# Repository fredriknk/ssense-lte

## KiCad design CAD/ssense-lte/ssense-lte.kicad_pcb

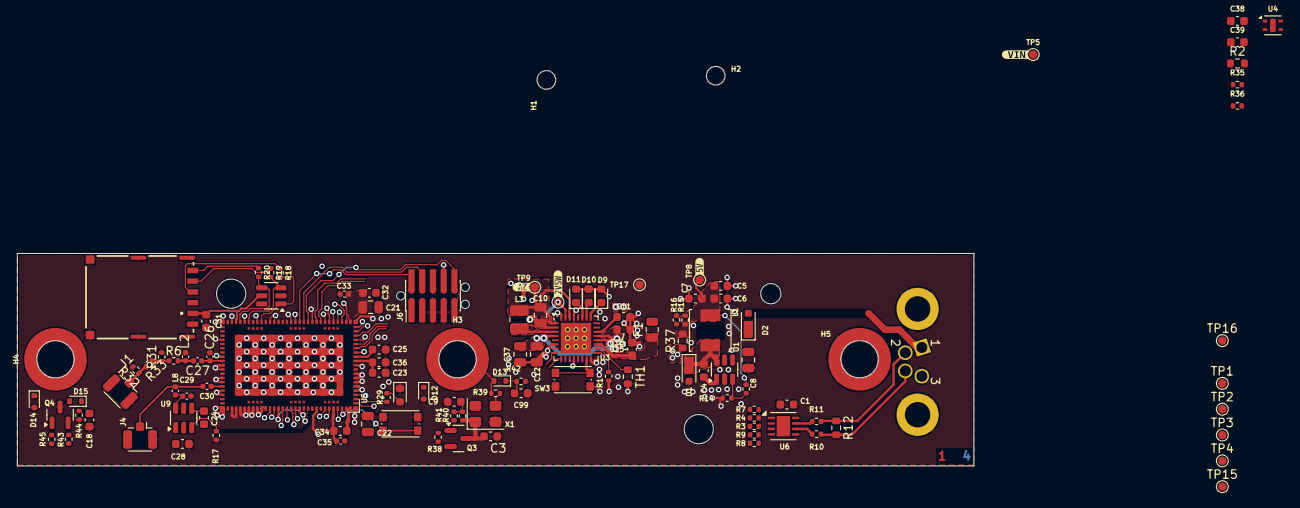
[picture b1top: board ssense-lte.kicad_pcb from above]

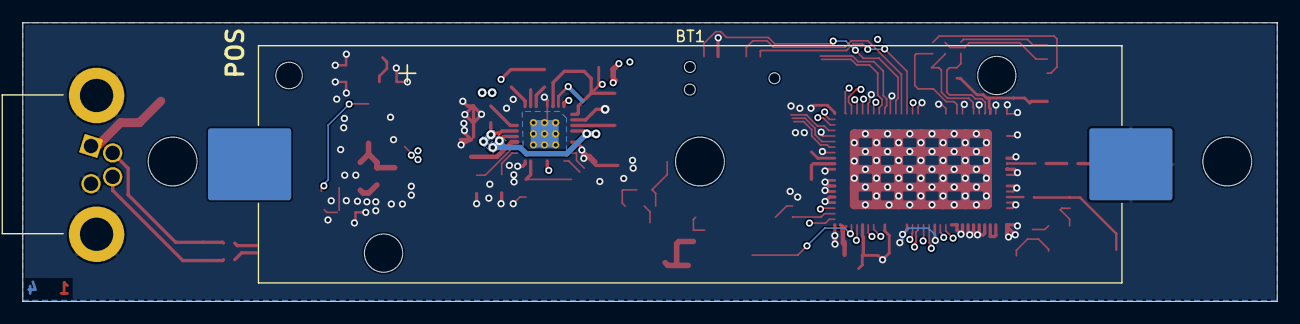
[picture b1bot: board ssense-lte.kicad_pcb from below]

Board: 4 copper layers, 113.0 x 25.1 mm, 123 parts (3 on the bottom side), 68 nets.

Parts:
BT1: Keystone 1042; BatteryHolder_Keystone_1042_1x18650
C1, C4, C32, C34, C36, C38: 0.1uF; C_0603_1608Metric
C3: 100nF; C_0603_1608Metric
C5, C6, C7, C15, C23, C25: 4.7uF; C_0603_1608Metric
C8: 2.2uF; C_0805_2012Metric
C9, C18, C24, C99: 1nF; C_0603_1608Metric
C10, C12, C37: 10uF; C_0805_2012Metric
C11, C16, C28, C31, C39: 1uF; C_0603_1608Metric
C21, C22: 47uF; C_0805_2012Metric
C26, C27, C33, C35: 15pF; C_0402_1005Metric_Sqr
C29, C30: 56pF; C_0402_1005Metric_Sqr
D1, D2: MSS1P3L-M3/89A; D_MicroSMP_AK
D7: LG L29K-G2J1-24-Z; LED_0603_1608Metric
D9, D10, D11: LED; LED_0603_1608Metric
D12, D14: Zener Prot 5V; D_SOD-523
D13, D15: CDSU101A; D_SOD-523
F1: 0805L110WR; Fuse_0805_2012Metric
H1, H2: MountingHole; MountingHole_2.2mm_M2
H3, H4, H5: 9774025360R; Mounting_Wuerth_WA-SMSI-M3_H2.5mm_9774025360
J1, J4: HIROSE ELECTRIC U.FL-R-SMT-1; U.FL_Hirose_U.FL-R-SMT-1_Vertical
J2: IEC61076-2_M8_A-coding_01x04_Receptacle_Shielded; STEWART_SS-12800-004_M8_04_Socket_Right_Angle
J3: 693043020611
J6: JLINK; SEXY_pinpogo
L1: 22uH; L_Abracon_AMDLA4020S
L2: 39NH; C_0402_1005Metric_Sqr
L3: 2.2uH; L_1008_2520Metric
L8: 68 nH; C_0402_1005Metric_Sqr
Q3: IRLML6401; SOT-23
Q4: MMBT3906; SOT-23
R1: 68k; R_0402_1005Metric
R2: 470R; R_0603_1608Metric
R3, R4, R14, R16, R35, R36, R38, R39, R40, R41, R43, R45: 10k; R_0402_1005Metric
R6, R7, R8, R9, R10, R11, R31, R32, R33: 0R; R_0402_1005Metric
R12: 120R; R_0603_1608Metric
R13: 56k; R_0402_1005Metric
R15: 15k; R_0402_1005Metric
R17, R42, R44: 1M; R_0402_1005Metric
R18, R19, R20: 100R; R_0402_1005Metric
R29: 150R; R_0402_1005Metric
R37: 0R; R_0603_1608Metric
SW1, SW3: KMR223NGLFG; SW_Push_1P1T_NO_CK_KMR2
TH1: 10k NTC; R_0603_1608Metric
TP1: SWDIO; TestPoint_Pad_D1.0mm
TP2: SWDCLK; TestPoint_Pad_D1.0mm
TP3: SWO; TestPoint_Pad_D1.0mm
TP4: RST; TestPoint_Pad_D1.0mm
TP5: VIN; TestPoint_Pad_D1.0mm
TP8: 5V; TestPoint_Pad_D1.0mm
TP9: 2V; TestPoint_Pad_D1.0mm
TP10: I1; TestPoint_Pad_D1.0mm
TP15, TP16, TP17: GND; TestPoint_Pad_D1.0mm
U1: LV2862XDDC; SOT-23-6
U3: nPM1300-QEXX; QFN-32-1EP_5x5mm_P0.5mm_EP3.6x3.6mm_ThermalVias
U4: SHTC3; Sensirion_DFN-4-1EP_2x2mm_P1mm_EP0.7x1.6mm
U5: nRF9160-SICA; LGA_9160_16.0x10.5mm
U6: THVD1450DR; VSON-8-1EP_3x3mm_P0.65mm_EP1.6x2.4mm
U8: USBLC6-4SC6; SOT-23-6
U9: TPS22917DBV; SOT-23-6
X1: KC3225K75.0000C1GE00; Oscillator_SMD_SeikoEpson_SG8002CE-4Pin_3.2x2.5mm
kibuzzard-680B6FC7: G***; kibuzzard-680B6FC7
kibuzzard-680B701D: G***; kibuzzard-680B701D
kibuzzard-680B714A: G***; kibuzzard-680B714A
kibuzzard-680B715D: G***; kibuzzard-680B715D
kibuzzard-689F1011: G***; kibuzzard-689F1011

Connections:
+1V8SIM: C31.1, J3.C1 (VCC), U5.49 (SIM_1V8), U8.5 (VBUS)
+3V3: C10.1, C23.1, C36.1, C38.1, C39.1, J6.1, L3.1, R35.2, R36.1, TP9.1, U3.1 (VOUT1), U3.12 (VDDIO), U3.30 (LSIN2/VINLDO2), U4.1 (VDD), U5.12 (VDD_GPIO)
+3V3SW: C1.1, TP10.1, U3.31 (LSOUT2/VOUTLDO2), U6.8 (VCC)
+3V6: Q3.2 (S), R38.1
+5V: C11.1, U3.22 (VBUSOUT)
+5VL: C16.1, R37.1, U3.21 (VBUS)
+12V: C8.1, D2.1 (K), U1.5 (VIN)
+BATT: C15.1, F1.1, U3.19 (VBAT)
/POWER/A': R10.1, U6.6 (A)
/POWER/A_P: J2.2, R11.2, R12.1
/POWER/B': R11.1, U6.7 (B)
/POWER/B_N: J2.4, R10.2, R12.2
/POWER/FB: R13.2, R14.1, U1.3 (FB)
/POWER/RE/DE': R3.2, R9.2, U6.2 (~RE), U6.3 (DE)
/POWER/RXD': R7.2, U6.1 (RO)
/POWER/SW: C4.2, D1.1 (K), L1.1, U1.6 (SW)
/POWER/SW1: L3.2, U3.3 (SW1)
/POWER/SW5V: C5.1, C6.1, C7.1, L1.2, R13.1, R15.1, R37.2, TP8.1
/POWER/TXD': R4.1, R8.2, U6.4 (DI)
/POWER/VIN: D2.2 (A), J2.1, TP5.1
/nrf9160/ANT: C26.1, C27.1, U5.61 (ANT)
/nrf9160/GPS_: C30.2, J4.1 (In), L8.1
COEX0: R17.2, U5.93 (COEX0), U9.3 (ON)
GND: BT1.2 (-), C1.2, C3.2, C5.2, C6.2, C7.2, C8.2, C9.2, C10.2, C11.2, C12.2, C15.2, C16.2, C18.2, C21.2, C22.2, C23.2, C25.2, C26.2, C28.2, C29.2, C31.2, C32.2, C33.2, C34.2, C35.2, C36.2, C37.2, C38.2, C39.2, C99.2, D1.2 (A), D7.1 (K), D12.2 (A), D14.2 (A), H5.1, J1.2 (Ext), J2.3, J2.SH, J3.C5 (GND), J3.S1, J3.S2, J3.S3, J3.S4, J3.S5, J3.S6, J4.2 (Ext), J6.3, J6.5, J6.7, J6.8, J6.9, L2.2, Q4.3 (C), R1.2, R2.2, R3.1, R14.2, R16.2, R17.1, R31.2, R32.2, R41.1, R42.2, R44.2, SW1.2, SW3.2, TH1.1, TP15.1, TP16.1, TP17.1, U1.2 (GND), U3.2 (PVSS1), U3.6 (PVSS2), U3.16 (VSET2), U3.29 (LSOUT1/VOUTLDO1), U3.33 (AVSS), U4.4 (VSS), U5.1 (GND_Shield), U5.5 (GND_Shield), U5.6 (GND_Shield), U5.7 (GND_Shield), U5.8 (GND_Shield), U5.9 (GND_Shield), U5.11 (GND_Shield), U5.14 (GND_Shield), U5.17 (GND_Shield), U5.21 (GND_Shield), U5.27 (GND_Shield), U5.31 (GND_Shield), U5.36 (GND_Shield), U5.41 (GND_Shield), U5.44 (GND_Shield), U5.47 (GND_Shield), U5.50 (GND_Shield), U5.52 (GND_Shield), U5.56 (GND_Shield), U5.60 (GND_Shield), U5.62 (GND_Shield), U5.63 (GND_Shield), U5.65 (GND_Shield), U5.66 (GND_Shield), U5.68 (GND_Shield), U5.69 (GND_Shield), U5.72 (GND_Shield), U5.74 (GND_Shield), U5.75 (GND_Shield), U5.76 (GND_Shield), U5.77 (GND_Shield), U5.78 (GND_Shield), U5.79 (GND_Shield), U5.80 (GND_Shield), U5.81 (GND_Shield), U5.82 (GND_Shield), U5.85 (GND_Shield), U5.90 (GND_Shield), U5.94 (GND_Shield), U5.98 (GND_Shield), U5.103 (VSS), U6.5 (GND), U8.2 (GND), U9.2 (GND), X1.2 (GND)
HF_OSC: Q3.1 (G), R38.2
unnamed: BT1.1 (+), F1.2
unnamed: C27.2, L2.1, R6.2
unnamed: D7.2 (A), R29.1
unnamed: D9.1 (K), U3.25 (LED0)
unnamed: D10.1 (K), U3.26 (LED1)
unnamed: D11.1 (K), U3.27 (LED2)
unnamed: D12.1 (K), D13.2 (A), H3.1, R39.2
unnamed: D14.1 (K), D15.2 (A), H4.1, Q4.2 (E), R43.2
unnamed: J1.1 (In), R32.1, R33.2
unnamed: J3.C3 (CLK), R19.1
unnamed: J3.C7 (I/O), R20.1
unnamed: J3.C2 (RST), R18.1
unnamed: C3.1, Q3.3 (D), R40.2, X1.1 (EN), X1.4 (Vdd)
unnamed: Q4.1 (B), R45.1
unnamed: R6.1, R31.1, R33.1
unnamed: C4.1, U1.1 (CB)
unnamed: TH1.2, U3.18 (NTC)
unnamed: SW3.1, U3.15 (SHPHLD)
unnamed: R1.1, U3.17 (VSET1)
unnamed: C25.1, U5.13 (DEC0)
unnamed: C30.1, U5.67 (GPS)
unnamed: C24.2, U9.4 (CT)
unnamed: C29.1, L8.2, U9.6 (VOUT)
unnamed: R39.1, X1.3 (OUT)
P0.04: SW1.1, U5.100 (P0.04)
P0.05: R15.2, R16.1, U5.2 (P0.05)
P0.06: R29.2, U5.3 (P0.06)
P0.11: U3.8 (GPIO1), U5.19 (P0.11)
P0.12: U3.9 (GPIO2), U5.20 (P0.12)
P0.28: R35.1, U3.13 (SDA), U4.3 (SDA), U5.86 (P0.28)
P0.29: R36.2, U3.14 (SCL), U4.2 (SCL), U5.87 (P0.29)
PWM: R43.1, R45.2
SENS_OUT: C18.1, D15.1 (K), R44.1
SENS_OUT_HF: C99.1, D13.1 (K), R42.1
SENS_OUT_HF_REF: C9.1, R40.1, R41.2
SIM_CLK: R19.2, U5.46 (SIM_CLK), U8.3 (I/O2)
SIM_IO: R20.2, U5.48 (SIM_IO), U8.4 (I/O3)
SIM_RST: R18.2, U5.43 (SIM_RST), U8.1 (I/O1)
SWDCLK: J6.4, TP2.1, U5.33 (SWDCLK)
SWDIO: J6.2, TP1.1, U5.34 (SWDIO)
SWO: J6.6, TP3.1, U5.95 (P0.00)
VCC: C12.1, C21.1, C22.1, C24.1, C28.1, C32.1, C33.1, C34.1, C35.1, C37.1, D9.2 (A), D10.2 (A), D11.2 (A), U3.4 (PVDD), U3.20 (VSYS), U3.32 (VOUT2), U5.22 (VDD2), U5.101 (ENABLE), U5.102 (VDD1), U9.1 (VIN)
~RESET: J6.10, TP4.1, U5.32 (~RESET)

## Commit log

2025-08-15 Feat: First push
2025-08-19 BcpPush
2025-08-19 Backup commit
